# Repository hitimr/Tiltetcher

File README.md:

# Tiltetcher
Project for builind a swinging etching tank with automated temperature regulation

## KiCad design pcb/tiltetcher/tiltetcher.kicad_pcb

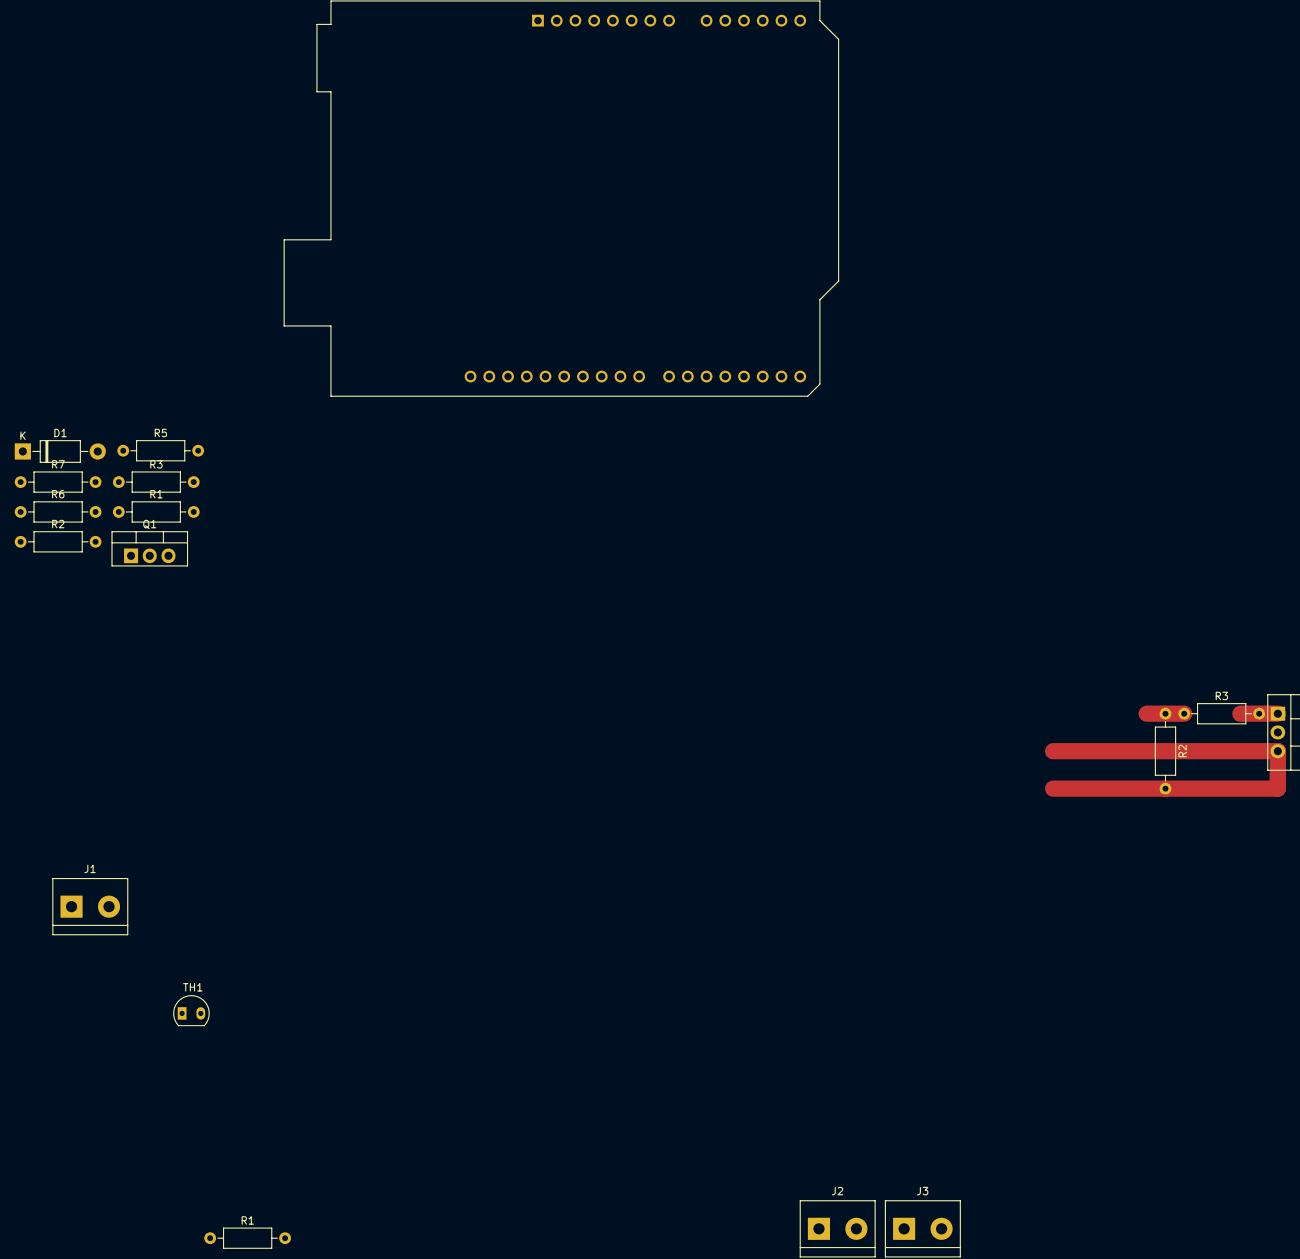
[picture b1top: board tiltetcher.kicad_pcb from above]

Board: 2 copper layers, 17 parts (0 on the bottom side), 9 nets.

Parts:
A1: Arduino_UNO_R3
D1: 1N4001; D_DO-41_SOD81_P10.16mm_Horizontal
J1: Peltier_Terminal; TerminalBlock_bornier-2_P5.08mm
J2: 12V_Terminal; TerminalBlock_bornier-2_P5.08mm
J3: Sensor_Terminal; TerminalBlock_bornier-2_P5.08mm
Q1: IRF640; TO-220-3_Vertical
Q1#2: IRF3205; TO-220-3_Vertical
R1, R1#2: 3k; R_Axial_DIN0207_L6.3mm_D2.5mm_P10.16mm_Horizontal
R2, R2#2, R3, R3#2: 1k; R_Axial_DIN0207_L6.3mm_D2.5mm_P10.16mm_Horizontal
R5, R6, R7: R220; R_Axial_DIN0207_L6.3mm_D2.5mm_P10.16mm_Horizontal
TH1: KTY10; SOD-70_P2.54mm

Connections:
+5V: A1.5 (+5V), D1.1 (K), J3.1, TH1.1
+12V: A1.8 (VIN), J2.1
/HEAT: R2#2.1, R3#2.1
/HEATER: R2.1, R3.1
/SENS: A1.9 (A0), J3.2, R1.1, R1#2.1, TH1.2
GND: A1.6 (GND), A1.7 (GND), A1.29 (GND), J2.2, Q1.3 (E), Q1#2.3 (S), R1.2, R1#2.2, R2.2, R2#2.2, R5.1, R6.1, R7.1
unnamed: D1.2 (A), Q1#2.2 (D)
unnamed: J1.2, Q1.2 (C)
unnamed: Q1.1 (B), Q1#2.1 (G), R3.2, R3#2.2

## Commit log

2022-07-16 datasheets
2022-07-16 clang format
2022-07-16 new SW structure
2022-07-16 added heater LED
2022-07-16 PIO Project
2022-07-16 added ISR TImer lib
2022-07-16 added timer
2022-07-16 spelling
2022-07-16 switched to simple timer
2022-07-16 bugfix
2022-07-16 added thermal sensor
2022-07-16 faster serial baud
2022-07-16 removed LED from timer
2022-07-16 heater is now working
2022-08-05 restructured heater
2022-08-05 moved files
2022-08-18 lcd temperature
2022-09-11 gpios are now switching correctly
2022-09-11 heater works!
